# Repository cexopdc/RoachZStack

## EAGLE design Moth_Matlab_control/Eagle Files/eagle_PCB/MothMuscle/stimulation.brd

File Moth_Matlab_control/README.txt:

### Eagle ###
Inside the eagle folder are the board and schematic files for the device. The board is marked with what the components are.

### Control Software ###
streamer.m is the control software. Run the matlab file and it will open a gui that controls the tool set. 

LED arena is controlled via serial port. 
1. Connect the USB cable from the arduino to the computer
2. Use the matlab script transmitLED.m to send a command to the arena
3. Commands are formatted as "x#" where x is either "f" or "b" and # is a digit written as a string. 
	The "f" or "b" set the direction, and the time sets the speed

EMG recording
Connect the CC2531 dongle to the computer. Make sure you can see it in device manager. In the streamer GUI, the left side is to control the ADC. Enter a time in the box, select the COM port that corresponds to the USB dongle and hit open. Inside the gui this calls the transmitADC.m file which sends a control character and the time to the CC2530. This should start streaming back data for the desired amount of time. 

Stimulation
The transmitStimulate.m function is called from the gui. Enter the parameters in the text boxes and hit stimulate. This function reads the parameters, and sends them and a control character to the CC2530. The stimulation is controlled via GPIO pins set. 

Here is a list of characters from 'A' to 'P'. These 16 characters control which combination of electrodes are desired. 

    case 'A':
      POS_STIM1_SBIT = 0;
      POS_STIM2_SBIT = 0;
      POS_STIM3_SBIT = 0;
      POS_STIM4_SBIT = 0;
      break;
    case 'B':
      POS_STIM1_SBIT = 1;
      POS_STIM2_SBIT = 0;
      POS_STIM3_SBIT = 0;
      POS_STIM4_SBIT = 0;
      break;
    case 'C':
      POS_STIM1_SBIT = 0;
      POS_STIM2_SBIT = 1;
      POS_STIM3_SBIT = 0;
      POS_STIM4_SBIT = 0;
      break;
     case 'D':
      POS_STIM1_SBIT = 1;
      POS_STIM2_SBIT = 1;
      POS_STIM3_SBIT = 0;
      POS_STIM4_SBIT = 0;
      break;
     case 'E':
      POS_STIM1_SBIT = 0;
      POS_STIM2_SBIT = 0;
      POS_STIM3_SBIT = 1;
      POS_STIM4_SBIT = 0;
      break;
    case 'F':
      POS_STIM1_SBIT = 1;
      POS_STIM2_SBIT = 0;
      POS_STIM3_SBIT = 1;
      POS_STIM4_SBIT = 0;
      break;
    case 'G':
      POS_STIM1_SBIT = 0;
      POS_STIM2_SBIT = 1;
      POS_STIM3_SBIT = 1;
      POS_STIM4_SBIT = 0;
      break;
     case 'H':
      POS_STIM1_SBIT = 1;
      POS_STIM2_SBIT = 1;
      POS_STIM3_SBIT = 1;
      POS_STIM4_SBIT = 0;
      break;
    case 'I':
      POS_STIM1_SBIT = 0;
      POS_STIM2_SBIT = 0;
      POS_STIM3_SBIT = 0;
      POS_STIM4_SBIT = 1;
      break;
    case 'J':
      POS_STIM1_SBIT = 1;
      POS_STIM2_SBIT = 0;
      POS_STIM3_SBIT = 0;
      POS_STIM4_SBIT = 1;
      break;
    case 'K':
      POS_STIM1_SBIT = 0;
      POS_STIM2_SBIT = 1;
      POS_STIM3_SBIT = 0;
      POS_STIM4_SBIT = 1;
      break;
     case 'L':
      POS_STIM1_SBIT = 1;
      POS_STIM2_SBIT = 1;
      POS_STIM3_SBIT = 0;
      POS_STIM4_SBIT = 1;
      break;
    case 'M':
      POS_STIM1_SBIT = 0;
      POS_STIM2_SBIT = 0;
      POS_STIM3_SBIT = 1;
      POS_STIM4_SBIT = 1;
      break;
    case 'N':
      POS_STIM1_SBIT = 1;
      POS_STIM2_SBIT = 0;
      POS_STIM3_SBIT = 1;
      POS_STIM4_SBIT = 1;
      break;
    case 'O':
      POS_STIM1_SBIT = 0;
      POS_STIM2_SBIT = 1;
      POS_STIM3_SBIT = 1;
      POS_STIM4_SBIT = 1;
      break;
     case 'P':
      POS_STIM1_SBIT = 1;
      POS_STIM2_SBIT = 1;
      POS_STIM3_SBIT = 1;
      POS_STIM4_SBIT = 1;
      break;

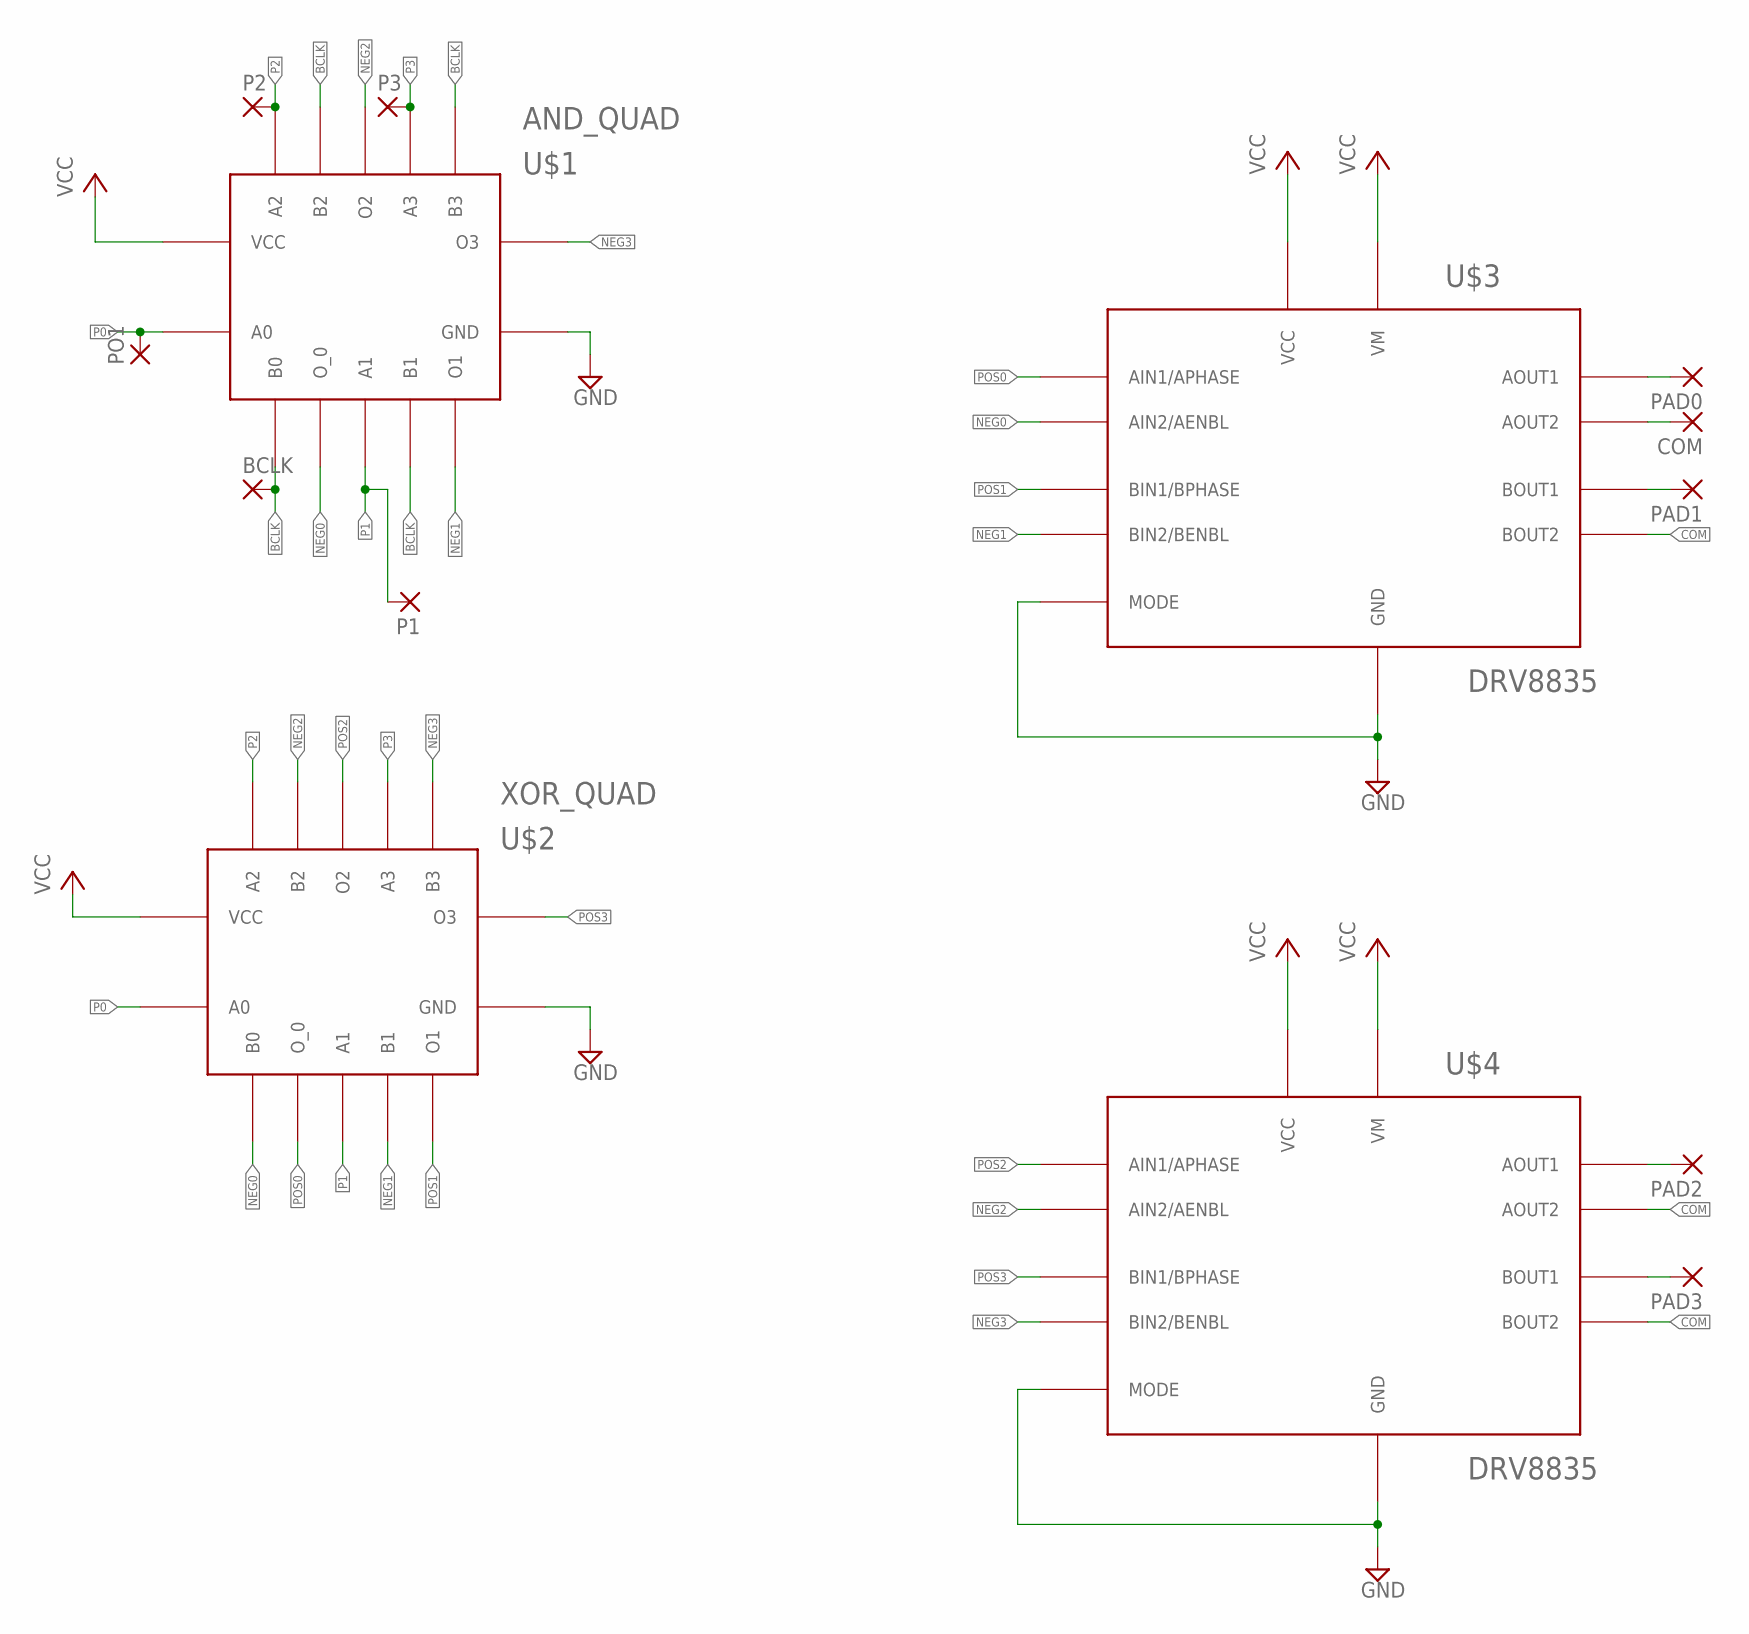
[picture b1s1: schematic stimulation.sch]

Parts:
BCLK: SMD2; SMD1,27-2,54
COM: SMD2; SMD1,27-2,54
P1, P2, P3: SMD2; SMD1,27-2,54
PAD0, PAD1, PAD2, PAD3: SMD2; SMD1,27-2,54
PO1: SMD2; SMD1,27-2,54
U$1: AND_QUAD; QFN-14
U$2: XOR_QUAD; QFN-14
U$3, U$4: DRV8835; QFN-12-HEATSINK

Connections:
BCLK: BCLK.1, U$1.B0, U$1.B1, U$1.B2, U$1.B3
COM: COM.1, U$3.AOUT2, U$3.BOUT2, U$4.AOUT2, U$4.BOUT2
GND: U$1.GND, U$2.GND, U$3.GND, U$3.MODE, U$4.GND, U$4.MODE
unnamed: P1.1, U$1.A1
unnamed: PAD0.1, U$3.AOUT1
unnamed: P2.1, U$1.A2
unnamed: PAD1.1, U$3.BOUT1
unnamed: P3.1, U$1.A3
unnamed: PO1.1, U$1.A0
unnamed: PAD2.1, U$4.AOUT1
unnamed: PAD3.1, U$4.BOUT1
NEG0: U$1.O_0, U$2.B0, U$3.AIN2.AENBL (AIN2/AENBL)
NEG1: U$1.O1, U$2.B1, U$3.BIN2/BENBL
NEG2: U$1.O2, U$2.B2, U$4.AIN2.AENBL (AIN2/AENBL)
NEG3: U$1.O3, U$2.B3, U$4.BIN2/BENBL
P0: U$2.A0
P1: U$2.A1
P2: U$2.A2
P3: U$2.A3
POS0: U$2.O_0, U$3.AIN1/APHASE
POS1: U$2.O1, U$3.BIN1/BPHASE
POS2: U$2.O2, U$4.AIN1/APHASE
POS3: U$2.O3, U$4.BIN1/BPHASE
VCC: U$1.VCC, U$2.VCC, U$3.VCC, U$3.VM, U$4.VCC, U$4.VM

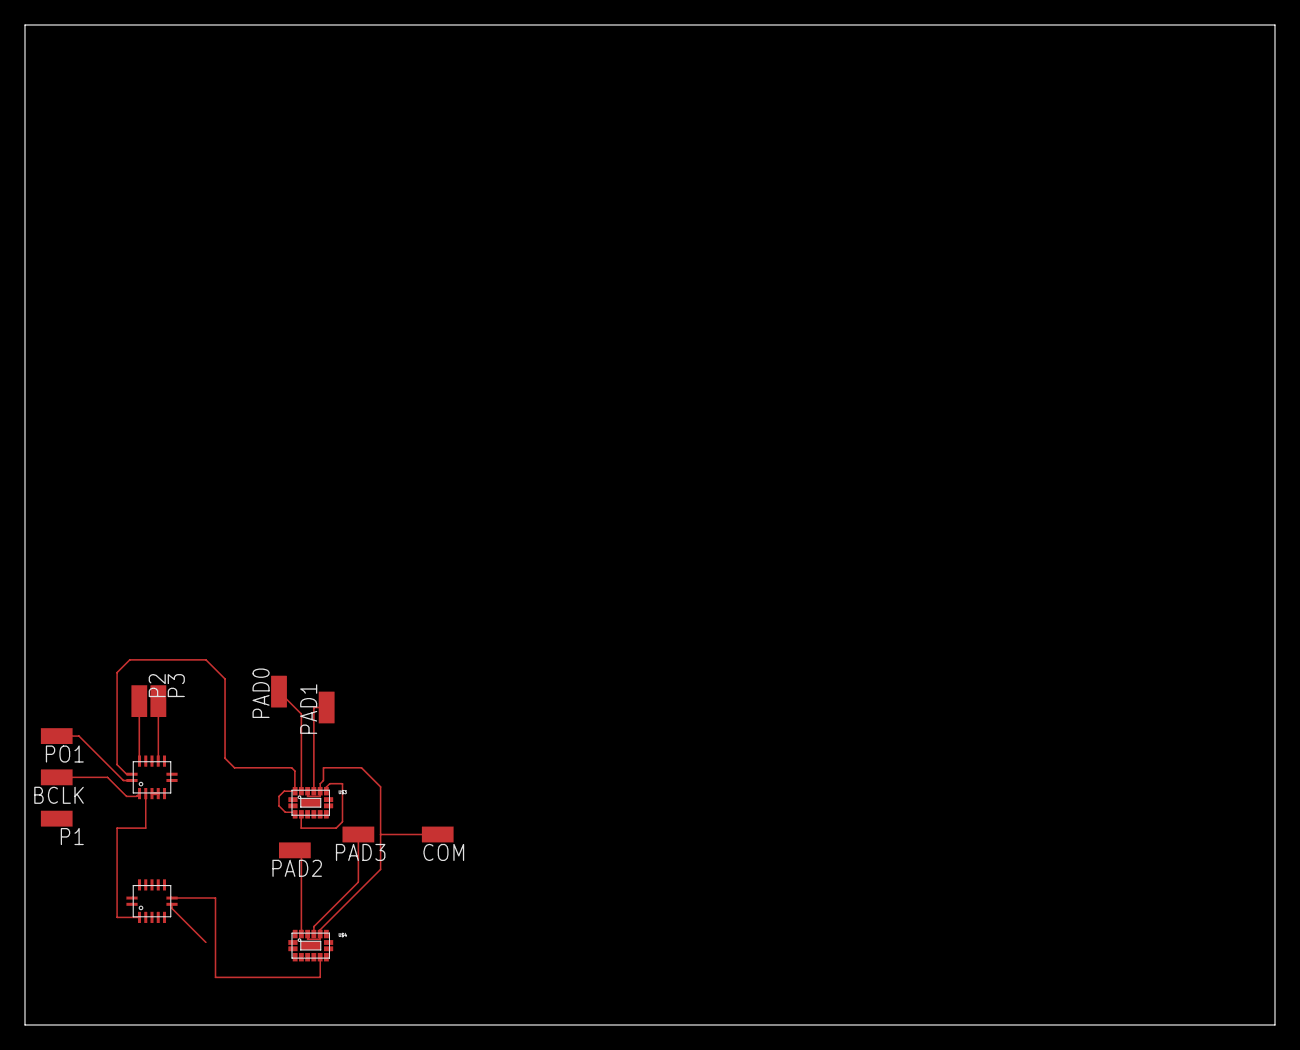
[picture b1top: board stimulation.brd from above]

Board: 2 copper layers, 100.0 x 80.0 mm, 14 parts (0 on the bottom side), 20 nets.

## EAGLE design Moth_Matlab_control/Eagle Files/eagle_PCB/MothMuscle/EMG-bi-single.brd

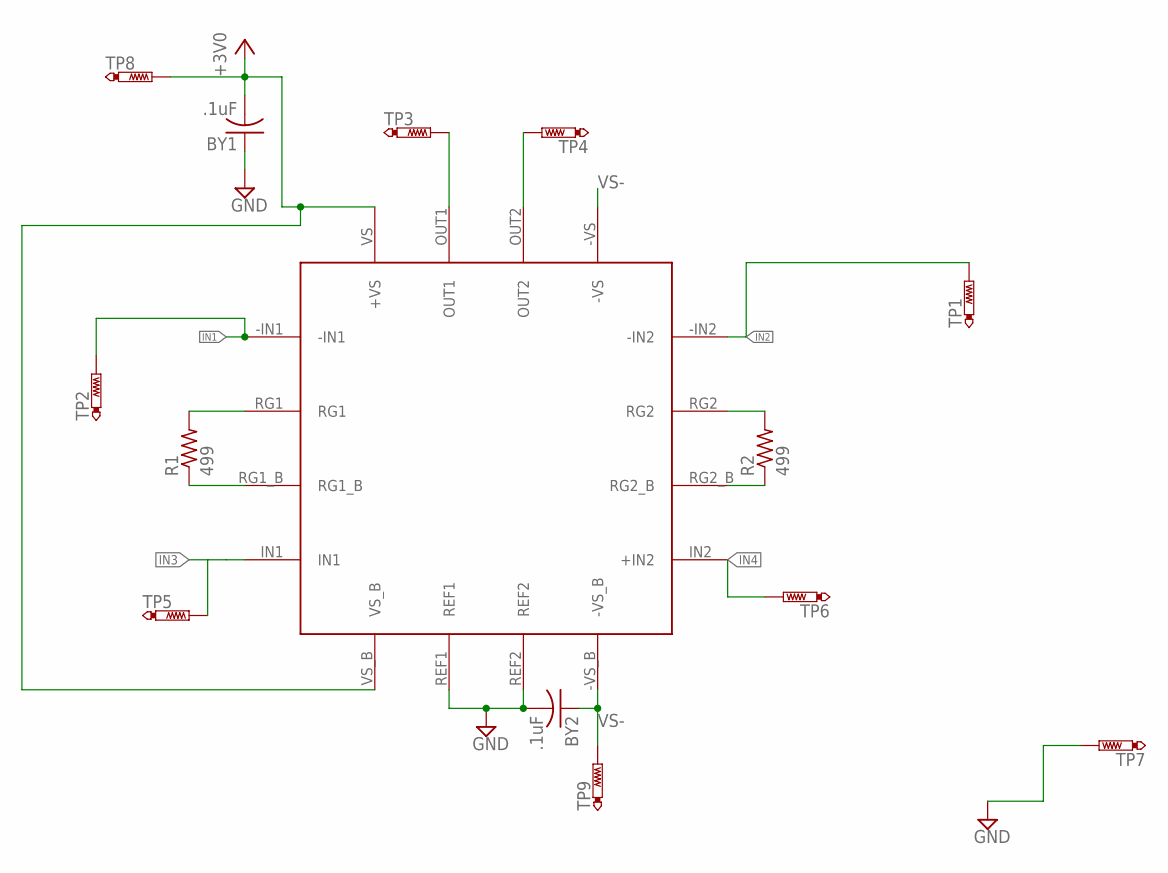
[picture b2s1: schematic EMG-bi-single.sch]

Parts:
BY1, BY2: .1uF; C0805
R1, R2: 499; R0805
TP1, TP2, TP3, TP4, TP5, TP6, TP7, TP8, TP9: PTR1TP20SQ; TP20SQ
U$9: AD8222; QFN-16

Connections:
+3V0: BY1.2, TP8.TP, U$9.VS (+VS), U$9.VS_B
GND: BY1.1, BY2.2, TP7.TP, U$9.REF1, U$9.REF2
IN1: TP2.TP, U$9.-IN1
IN2: TP1.TP, U$9.-IN2
IN3: TP5.TP, U$9.IN1
IN4: TP6.TP, U$9.IN2 (+IN2)
unnamed: R1.2, U$9.RG1
unnamed: R1.1, U$9.RG1_B
unnamed: R2.2, U$9.RG2
unnamed: TP3.TP, U$9.OUT1
unnamed: R2.1, U$9.RG2_B
unnamed: TP4.TP, U$9.OUT2
VS-: BY2.1, TP9.TP, U$9.-VS, U$9.-VS_B

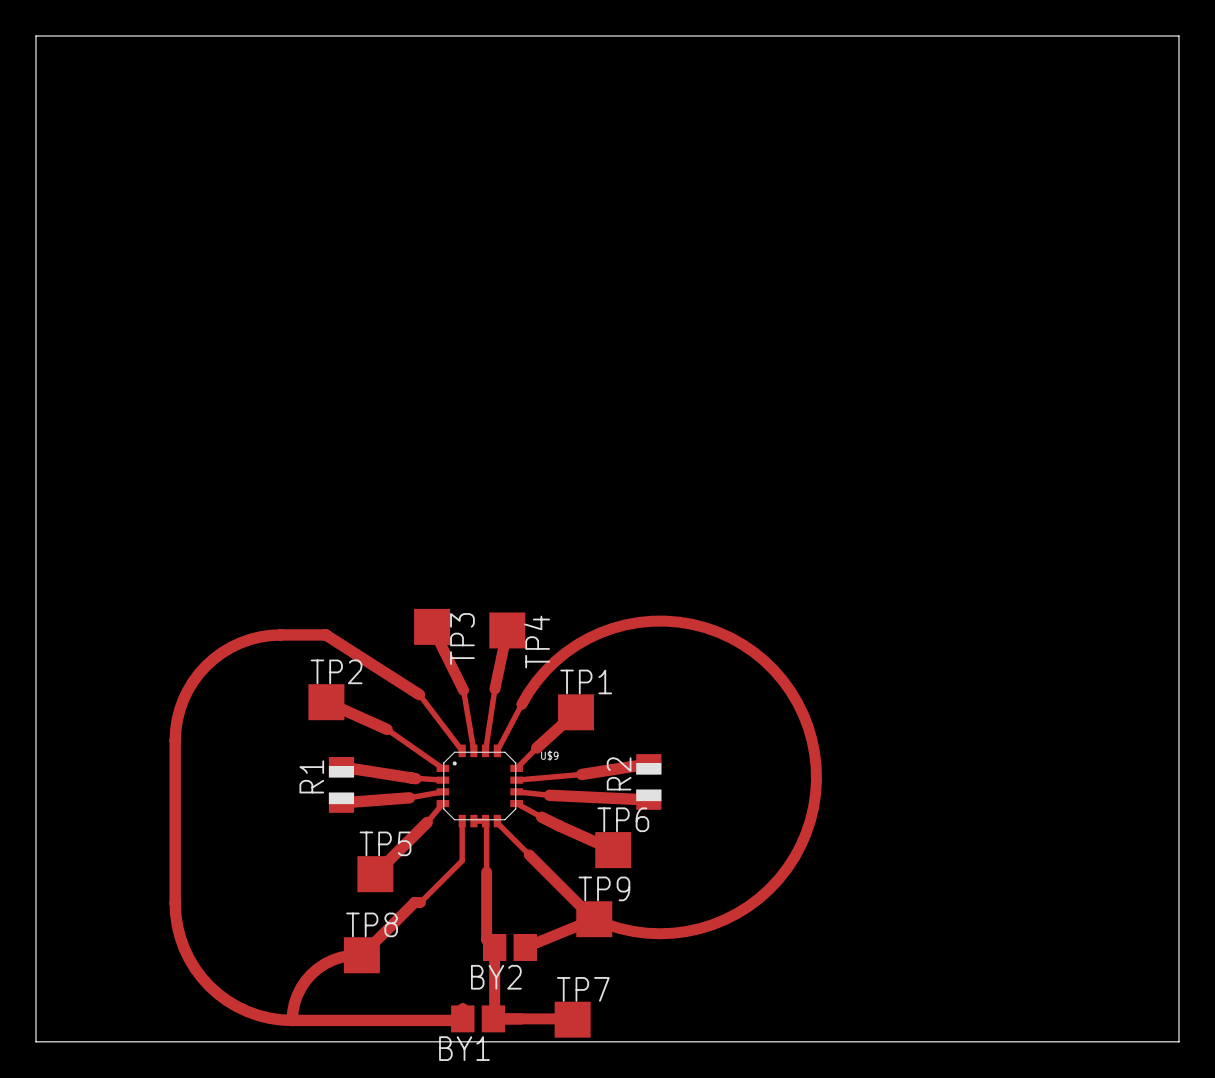
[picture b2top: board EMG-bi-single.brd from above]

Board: 2 copper layers, 63.5 x 55.9 mm, 14 parts (0 on the bottom side), 13 nets.

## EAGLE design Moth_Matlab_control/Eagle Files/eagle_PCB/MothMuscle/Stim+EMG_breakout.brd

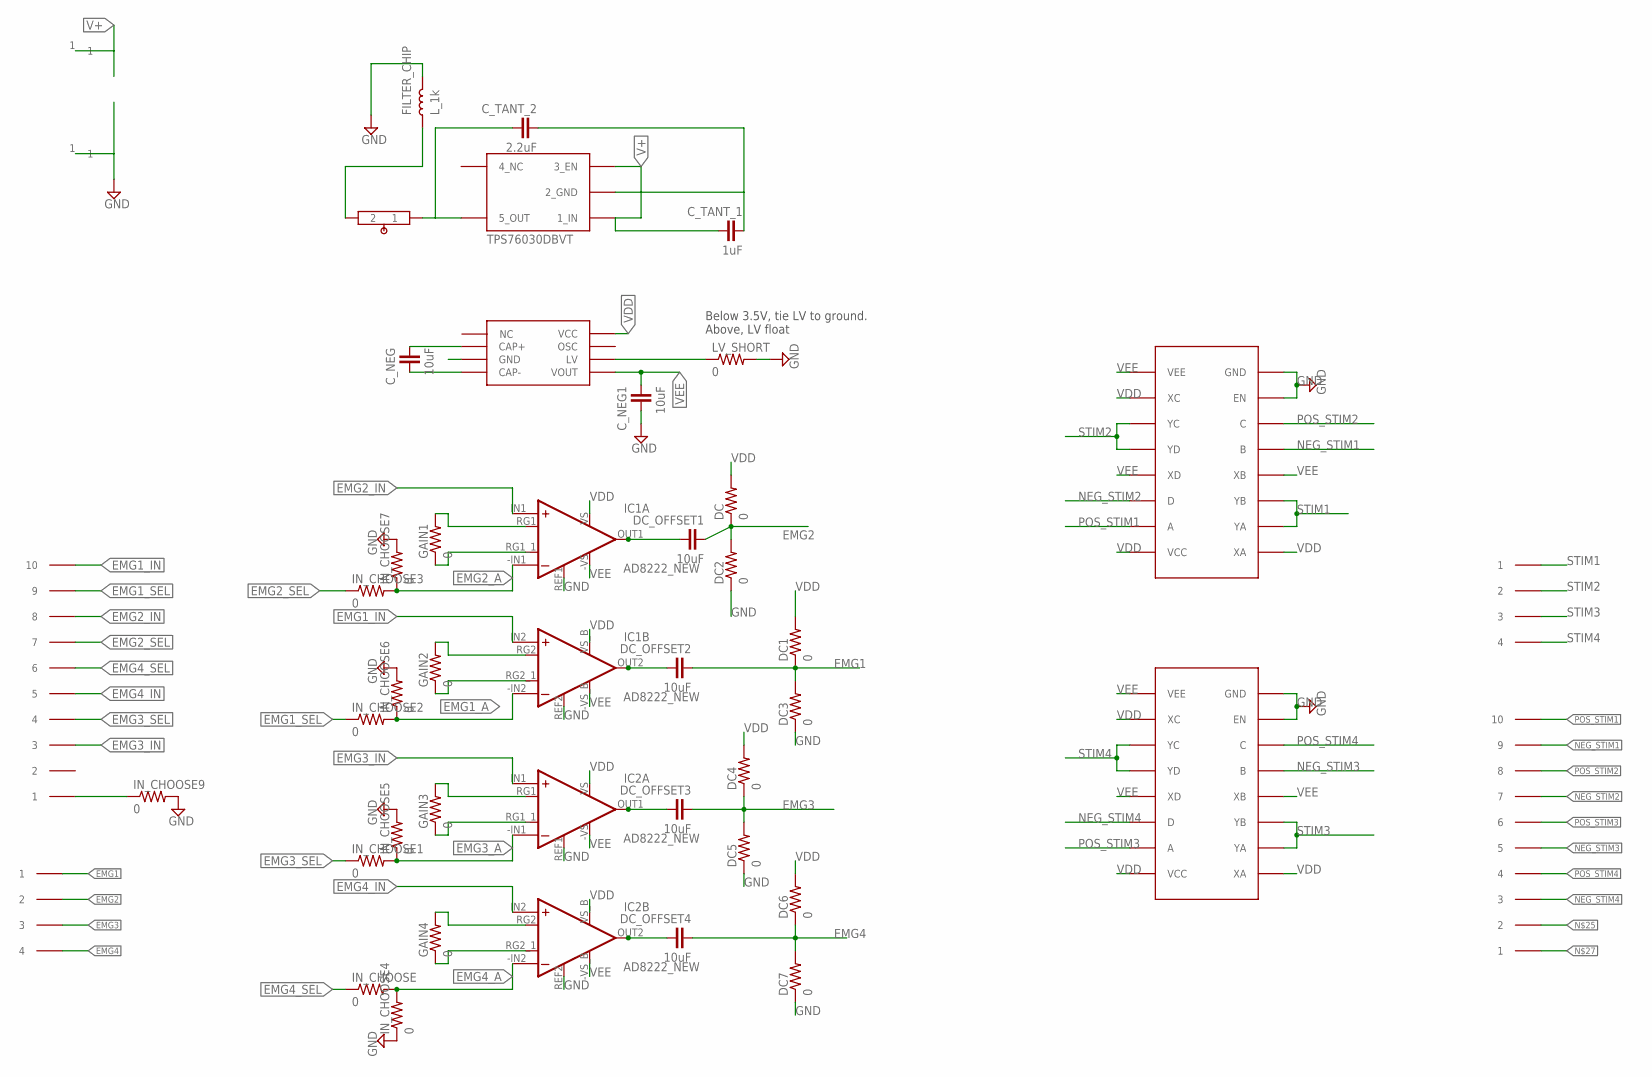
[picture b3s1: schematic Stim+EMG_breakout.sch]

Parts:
C_NEG, C_NEG1: 10uF; 0402_R/L/C
C_TANT_1: 1uF; 0603_R/L/C
C_TANT_2: 2.2uF; 0603_R/L/C
DC, DC1, DC2, DC3, DC4, DC5, DC6, DC7: 0; 0402_R/L/C
DC_OFFSET1, DC_OFFSET2, DC_OFFSET3, DC_OFFSET4: 10uF; 0402_R/L/C
FILTER_CHIP: L_1k; 0402_R/L/C
GAIN1, GAIN2, GAIN3, GAIN4: 0; 0402_R/L/C
IC1, IC2: AD8222_NEW; QFN-16
IN_CHOOSE, IN_CHOOSE1, IN_CHOOSE2, IN_CHOOSE3, IN_CHOOSE4, IN_CHOOSE5, IN_CHOOSE6, IN_CHOOSE7, IN_CHOOSE9: 0; 0201_R/L/C
LV_SHORT: 0; 0402_R/L/C
U$1, U$7: FFC10POS
U$2, U$28: FFC4POS
U$4: TL7660; S-PDSO-G8
U$5, U$6: MC74HC4316A; SOIC-16-ON-SEMI
U$10: REGULATOR
U$18: SWITCH_MANUAL
WIRE+: DRILL_CONNECT
WIRE-: DRILL_CONNECT

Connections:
EMG1: DC1.1, DC3.2, DC_OFFSET2.2, U$2.1
EMG1_A: IC1.-IN2 (-IN), IN_CHOOSE2.2, IN_CHOOSE6.1
EMG1_IN: IC1.IN2 (+IN), U$7.10
EMG1_SEL: IN_CHOOSE2.1, U$7.9
EMG2: DC.1, DC2.2, DC_OFFSET1.2, U$2.2
EMG2_A: IC1.-IN1 (-IN), IN_CHOOSE3.2, IN_CHOOSE7.1
EMG2_IN: IC1.IN1 (+IN), U$7.8
EMG2_SEL: IN_CHOOSE3.1, U$7.7
EMG3: DC4.1, DC5.2, DC_OFFSET3.2, U$2.3
EMG3_A: IC2.-IN1 (-IN), IN_CHOOSE1.2, IN_CHOOSE5.1
EMG3_IN: IC2.IN1 (+IN), U$7.3
EMG3_SEL: IN_CHOOSE1.1, U$7.4
EMG4: DC6.1, DC7.2, DC_OFFSET4.2, U$2.4
EMG4_A: IC2.-IN2 (-IN), IN_CHOOSE.2, IN_CHOOSE4.2
EMG4_IN: IC2.IN2 (+IN), U$7.5
EMG4_SEL: IN_CHOOSE.1, U$7.6
GND: C_NEG1.1, DC2.1, DC3.1, DC5.1, DC7.1, FILTER_CHIP.2, IC1.REF1 (REF), IC1.REF2 (REF), IC2.REF1 (REF), IC2.REF2 (REF), IN_CHOOSE4.1, IN_CHOOSE5.2, IN_CHOOSE6.2, IN_CHOOSE7.2, IN_CHOOSE9.2, LV_SHORT.2, U$4.3 (GND), U$5.7 (EN), U$5.8 (GND), U$6.7 (EN), U$6.8 (GND), WIRE-.1
unnamed: C_NEG.2, U$4.2 (CAP+)
unnamed: C_NEG.1, U$4.4 (CAP-)
unnamed: LV_SHORT.1, U$4.6 (LV)
unnamed: GAIN1.2, IC1.RG1
unnamed: GAIN1.1, IC1.RG1_1
unnamed: GAIN2.2, IC1.RG2 (RG1)
unnamed: GAIN2.1, IC1.RG2_1 (RG1_1)
unnamed: GAIN3.2, IC2.RG1
unnamed: GAIN3.1, IC2.RG1_1
unnamed: GAIN4.2, IC2.RG2 (RG1)
unnamed: GAIN4.1, IC2.RG2_1 (RG1_1)
unnamed: DC_OFFSET1.1, IC1.OUT1 (OUT)
unnamed: DC_OFFSET2.1, IC1.OUT2 (OUT)
unnamed: DC_OFFSET4.1, IC2.OUT2 (OUT)
unnamed: DC_OFFSET3.1, IC2.OUT1 (OUT)
unnamed: C_TANT_2.1, U$10.5 (5_OUT), U$18.1
unnamed: C_TANT_1.2, C_TANT_2.2, U$10.2 (2_GND)
unnamed: IN_CHOOSE9.1, U$7.1
NC: U$4.1 (NC)
NEG_STIM1: U$1.9, U$5.5 (B)
NEG_STIM2: U$1.7, U$5.14 (D)
NEG_STIM3: U$1.5, U$6.5 (B)
NEG_STIM4: U$1.3, U$6.14 (D)
OSC: U$4.7 (OSC)
POS_STIM1: U$1.10, U$5.15 (A)
POS_STIM2: U$1.8, U$5.6 (C)
POS_STIM3: U$1.6, U$6.15 (A)
POS_STIM4: U$1.4, U$6.6 (C)
STIM1: U$5.2 (YA), U$5.3 (YB), U$28.1
STIM2: U$5.11 (YC), U$5.12 (YD), U$28.2
STIM3: U$6.2 (YA), U$6.3 (YB), U$28.3
STIM4: U$6.11 (YC), U$6.12 (YD), U$28.4
V+: C_TANT_1.1, U$10.1 (1_IN), U$10.3 (3_EN), WIRE+.1
VDD: DC.2, DC1.2, DC4.2, DC6.2, FILTER_CHIP.1, IC1.VS (V+), IC1.VS_B (V+), IC2.VS (V+), IC2.VS_B (V+), U$4.8 (VCC), U$5.1 (XA), U$5.10 (XC), U$5.16 (VCC), U$6.1 (XA), U$6.10 (XC), U$6.16 (VCC), U$18.2
VEE: C_NEG1.2, IC1.-VS (V-), IC1.-VS_B (V-), IC2.-VS (V-), IC2.-VS_B (V-), U$4.5 (VOUT), U$5.4 (XB), U$5.9 (VEE), U$5.13 (XD), U$6.4 (XB), U$6.9 (VEE), U$6.13 (XD)

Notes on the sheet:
Below 3.5V, tie LV to ground. Above, LV float

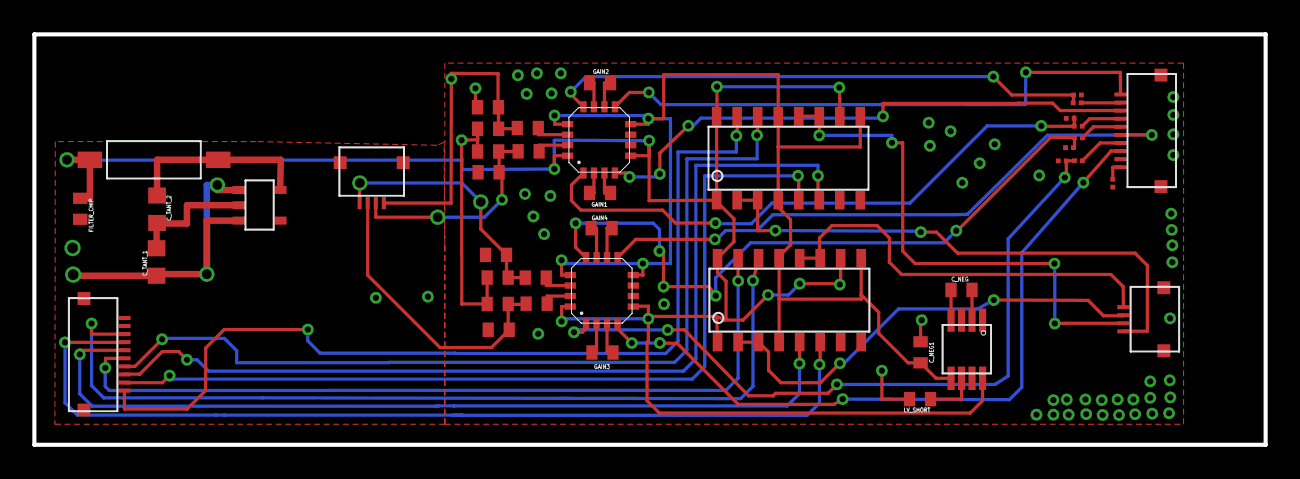
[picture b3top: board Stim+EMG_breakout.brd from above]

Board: 2 copper layers, 76.2 x 25.4 mm, 44 parts (0 on the bottom side), 50 nets.

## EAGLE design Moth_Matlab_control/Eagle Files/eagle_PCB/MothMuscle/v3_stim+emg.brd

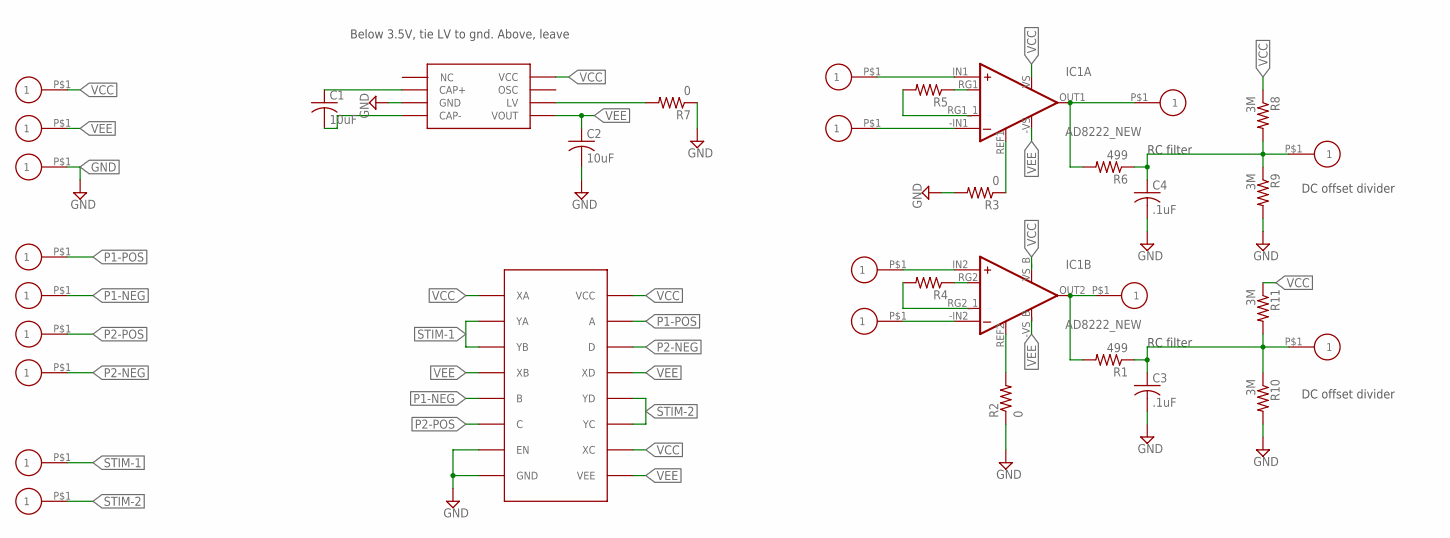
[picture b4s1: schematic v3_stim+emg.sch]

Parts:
A+: DBG_ELECTRODE
A-: DBG_ELECTRODE
A-OUT: DBG_ELECTRODE
B+: DBG_ELECTRODE
B-: DBG_ELECTRODE
B-OUT: DBG_ELECTRODE
C1, C2: 10uF; C0402
C3, C4: .1uF; C0402
EMG1, EMG2: DBG_ELECTRODE
GND: DBG_ELECTRODE
IC1: AD8222_NEW; QFN-16
P1-NEG, P1-POS, P2-NEG, P2-POS: DBG_ELECTRODE
R1, R6: 499; R0402
R2, R3, R7: 0; R0402
R4, R5: R-US_R0402; R0402
R8, R9, R10, R11: 3M; R0402
STIM-1, STIM-2: DBG_ELECTRODE
U$1: MC74HC4316A; SOIC-16-ON-SEMI
U$2: TL7660; S-PDSO-G8
VCC: DBG_ELECTRODE
VEE: DBG_ELECTRODE

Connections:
EMG1: C4.1, EMG1.P$1, R6.1, R8.2, R9.1
EMG2: C3.1, EMG2.P$1, R1.1, R10.1, R11.2
GND: C2.2, C3.2, C4.2, GND.P$1, R2.1, R3.2, R7.1, R9.2, R10.2, U$1.7 (EN), U$1.8 (GND), U$2.3 (GND)
unnamed: C1.1, U$2.2 (CAP+)
unnamed: C1.2, U$2.4 (CAP-)
unnamed: B+.P$1, IC1.IN2 (+IN)
unnamed: B-.P$1, IC1.-IN2 (-IN)
unnamed: R7.2, U$2.6 (LV)
unnamed: B-OUT.P$1, IC1.OUT2 (OUT), R1.2
unnamed: IC1.RG2 (RG1), R4.1
unnamed: IC1.RG2_1 (RG1_1), R4.2
unnamed: IC1.REF1 (REF), R3.1
unnamed: IC1.RG1, R5.1
unnamed: IC1.RG1_1, R5.2
unnamed: IC1.REF2 (REF), R2.2
unnamed: A-OUT.P$1, IC1.OUT1 (OUT), R6.2
unnamed: A+.P$1, IC1.IN1 (+IN)
unnamed: A-.P$1, IC1.-IN1 (-IN)
NC: U$2.1 (NC)
OSC: U$2.7 (OSC)
P1-NEG: P1-NEG.P$1, U$1.5 (B)
P1-POS: P1-POS.P$1, U$1.15 (A)
P2-NEG: P2-NEG.P$1, U$1.14 (D)
P2-POS: P2-POS.P$1, U$1.6 (C)
STIM-1: STIM-1.P$1, U$1.2 (YA), U$1.3 (YB)
STIM-2: STIM-2.P$1, U$1.11 (YC), U$1.12 (YD)
VCC: IC1.VS (V+), IC1.VS_B (V+), R8.1, R11.1, U$1.1 (XA), U$1.10 (XC), U$1.16 (VCC), U$2.8 (VCC), VCC.P$1
VEE: C2.1, IC1.-VS (V-), IC1.-VS_B (V-), U$1.4 (XB), U$1.9 (VEE), U$1.13 (XD), U$2.5 (VOUT), VEE.P$1

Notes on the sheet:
Below 3.5V, tie LV to gnd. Above, leave
DC offset divider
RC filter

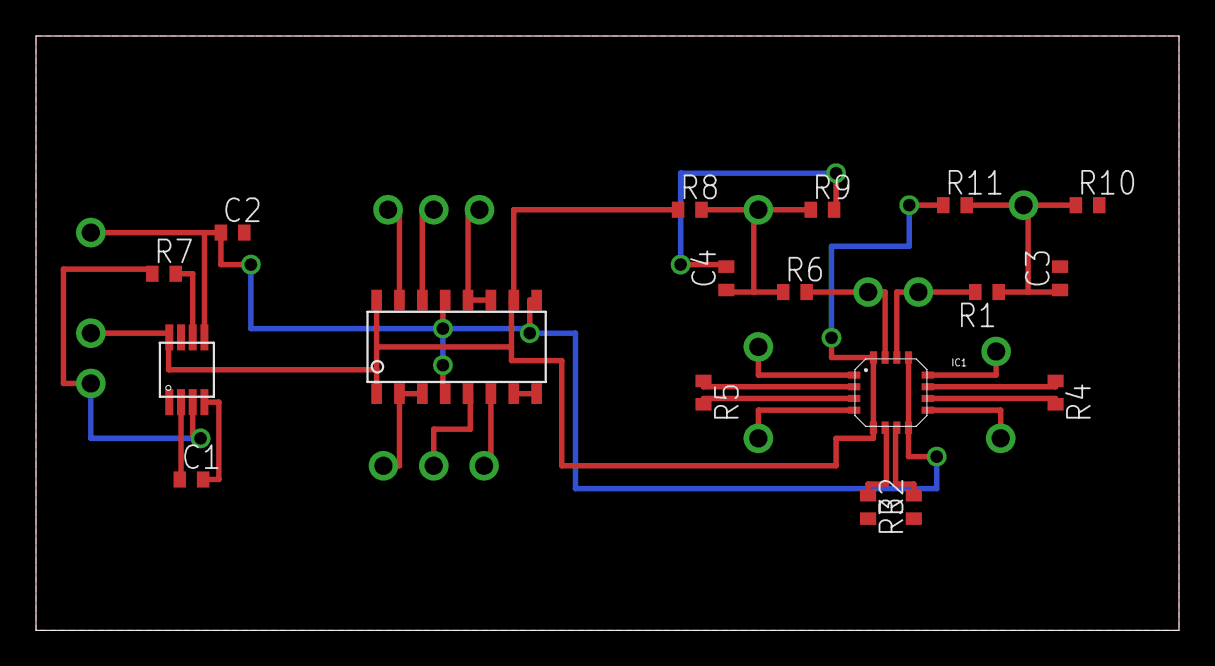
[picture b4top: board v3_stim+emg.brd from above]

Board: 2 copper layers, 63.5 x 33.0 mm, 35 parts (0 on the bottom side), 26 nets.

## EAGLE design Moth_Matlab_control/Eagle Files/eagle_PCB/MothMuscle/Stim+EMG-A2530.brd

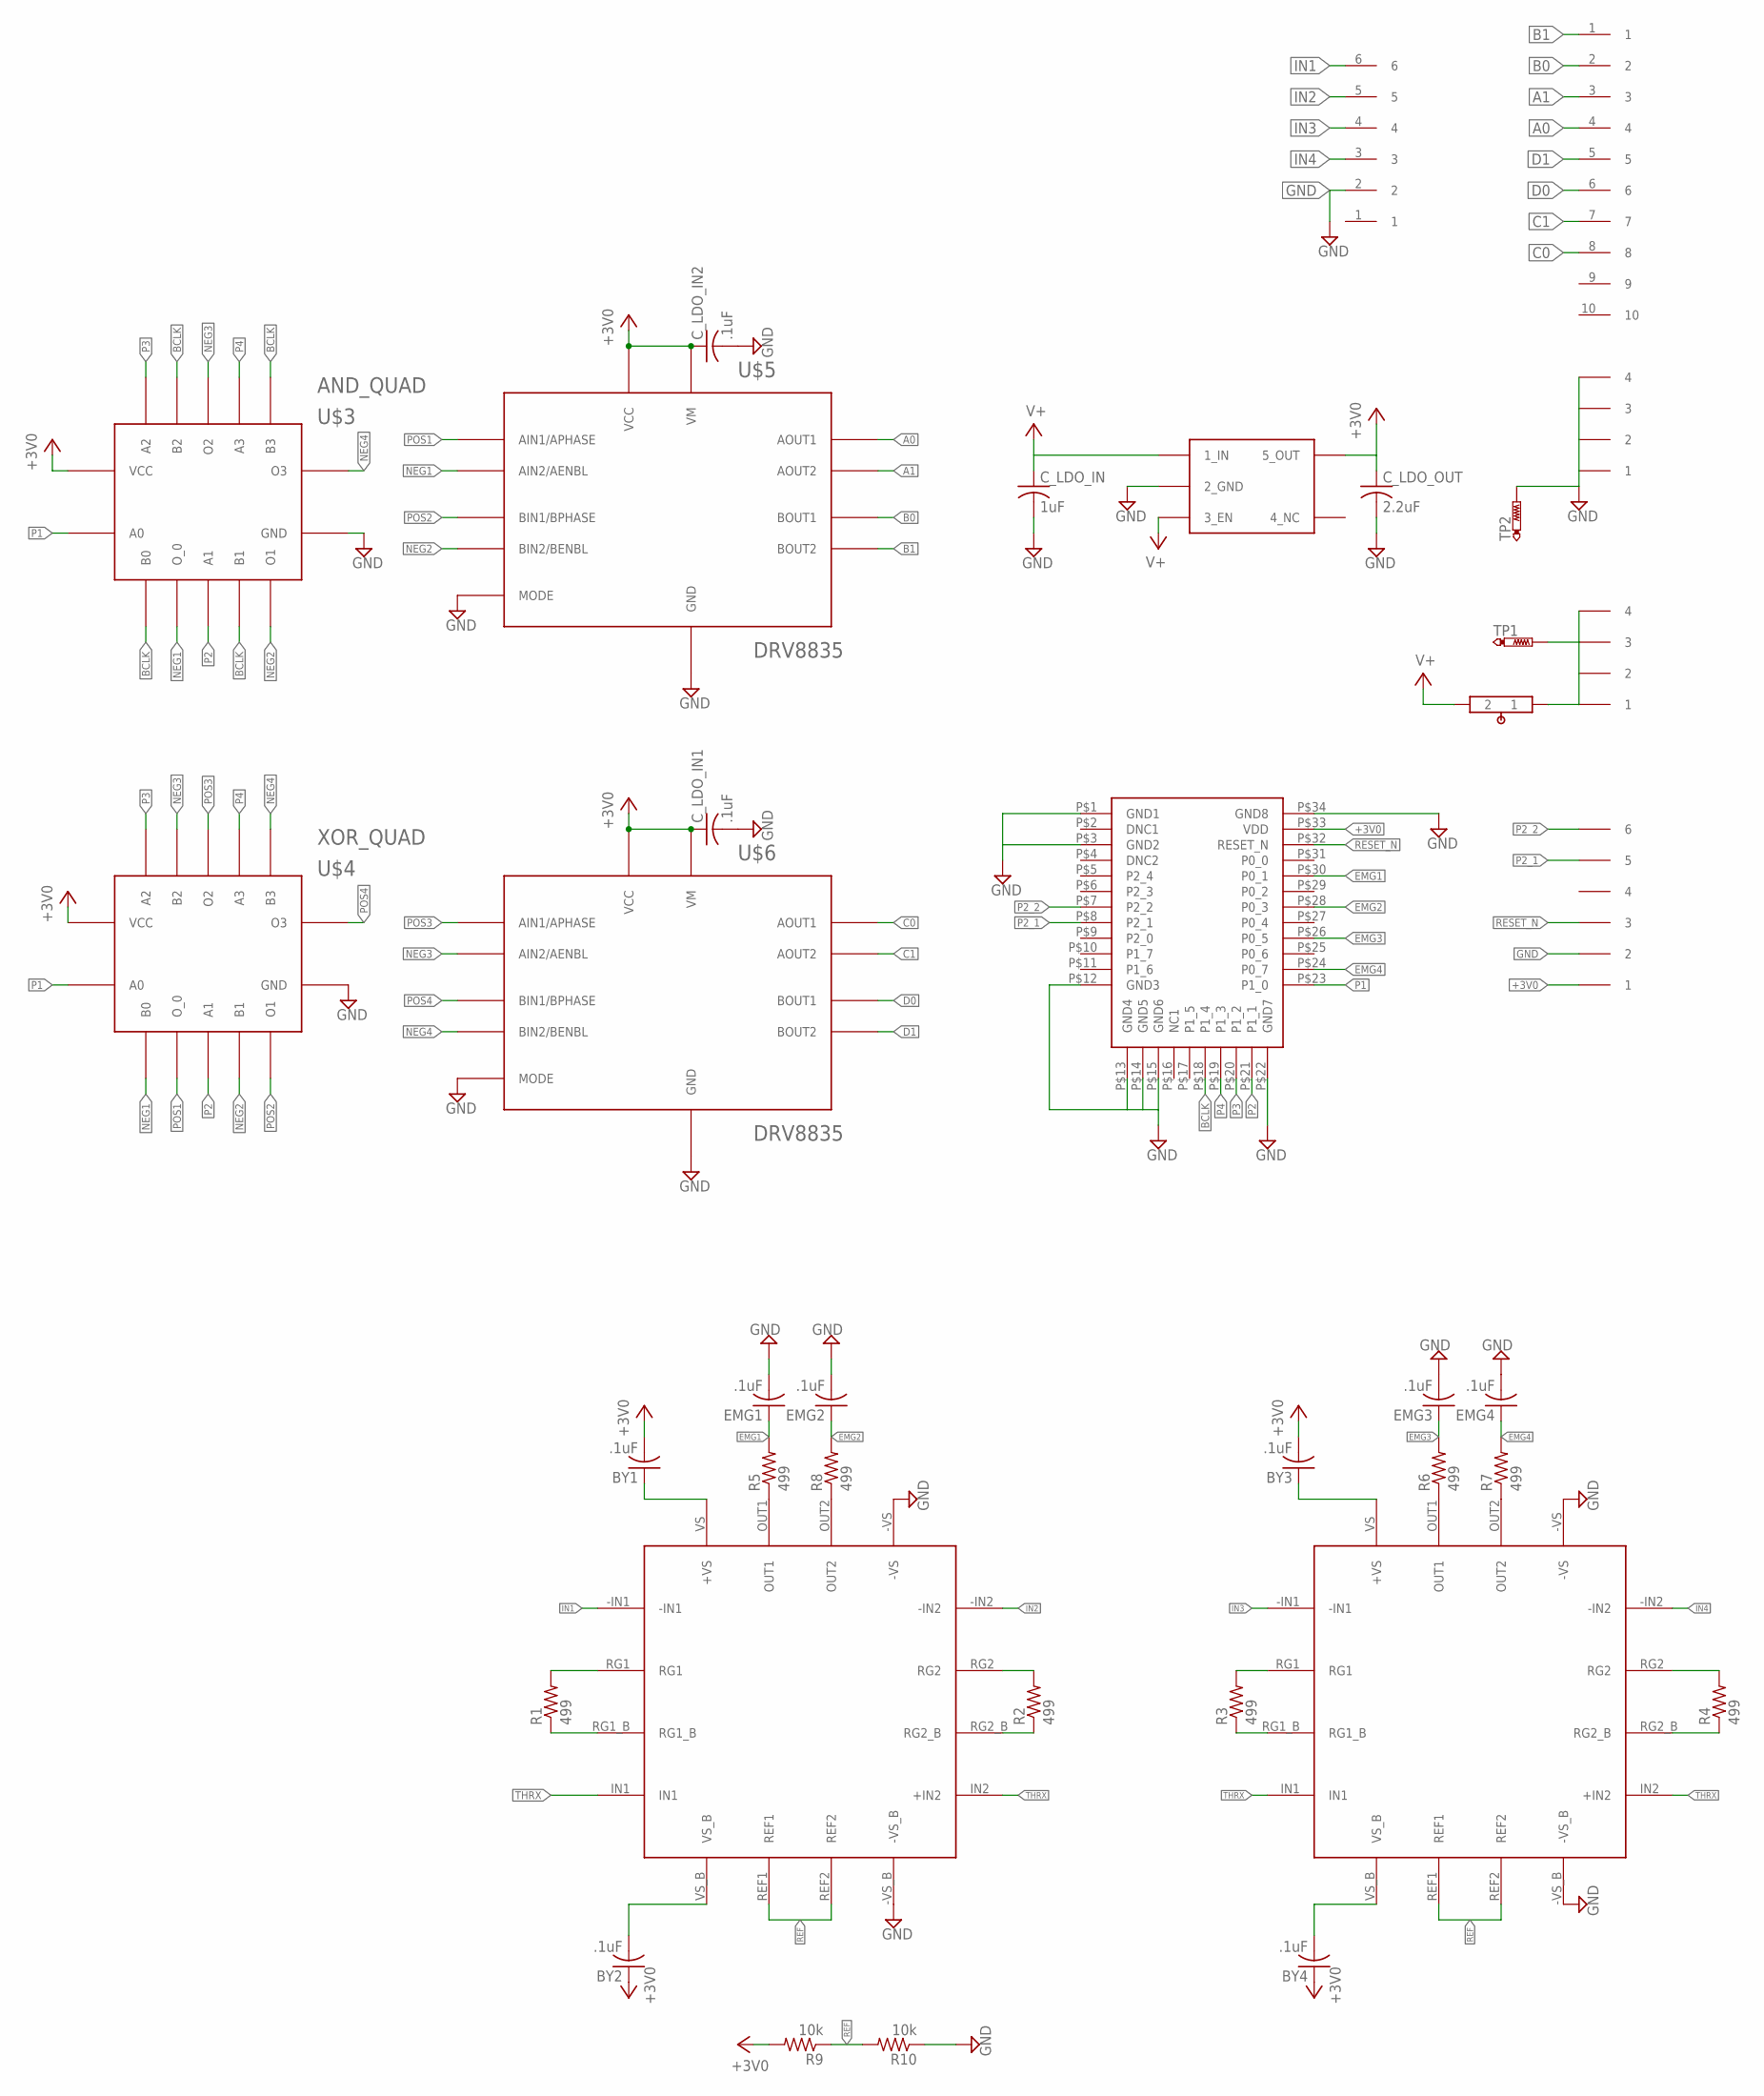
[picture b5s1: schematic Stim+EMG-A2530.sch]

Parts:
BY1, BY2, BY3, BY4: .1uF; C0603
C_LDO_IN: 1uF; C0603
C_LDO_IN1, C_LDO_IN2: .1uF; C0603
C_LDO_OUT: 2.2uF; C0603
EMG1, EMG2, EMG3, EMG4: .1uF; C0603
R1, R2, R3, R4, R5, R6, R7, R8: 499; R0402
R9, R10: 10k; R0402
TP1, TP2: PTR1B2,54; B2,54
U$1: A2530
U$2, U$12: FFC6POS
U$3: AND_QUAD; QFN-14
U$4: XOR_QUAD; QFN-14
U$5, U$6: DRV8835; QFN-12-HEATSINK
U$7, U$8: FFC4POS
U$9, U$10: AD8222; QFN-16
U$11: FFC10POS
U$18: SWITCH_MANUAL
VREG1: REGULATOR

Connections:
+3V0: C_LDO_OUT.1, U$1.P$33 (VDD), U$2.1, VREG1.5 (5_OUT)
+3V3: BY1.2, BY2.1, BY3.2, BY4.1, C_LDO_IN1.1, C_LDO_IN2.1, R9.2, U$3.VCC, U$4.VCC, U$5.VCC, U$5.VM, U$6.VCC, U$6.VM
A0: U$5.AOUT1, U$11.4
A1: U$5.AOUT2, U$11.3
B0: U$5.BOUT1, U$11.2
B1: U$5.BOUT2, U$11.1
BCLK: U$1.P$18 (P1_4), U$3.B0, U$3.B1, U$3.B2, U$3.B3
C0: U$6.AOUT1, U$11.8
C1: U$6.AOUT2, U$11.7
D0: U$6.BOUT1, U$11.6
D1: U$6.BOUT2, U$11.5
EMG1: EMG1.1, R5.2, U$1.P$30 (P0_1)
EMG2: EMG2.1, R8.2, U$1.P$28 (P0_3)
EMG3: EMG3.1, R6.2, U$1.P$26 (P0_5)
EMG4: EMG4.1, R7.2, U$1.P$24 (P0_7)
GND: C_LDO_IN.2, C_LDO_IN1.2, C_LDO_IN2.2, C_LDO_OUT.2, EMG1.2, EMG2.2, EMG3.2, EMG4.2, R10.1, TP2.TP, U$1.P$1 (GND1), U$1.P$3 (GND2), U$1.P$12 (GND3), U$1.P$13 (GND4), U$1.P$14 (GND5), U$1.P$15 (GND6), U$1.P$22 (GND7), U$1.P$34 (GND8), U$2.2, U$3.GND, U$4.GND, U$5.GND, U$5.MODE, U$6.GND, U$6.MODE, U$8.1, U$8.2, U$8.3, U$8.4, U$9.-VS, U$9.-VS_B, U$10.-VS, U$10.-VS_B, U$12.2, VREG1.2 (2_GND)
IN1: U$9.-IN1, U$12.6
IN2: U$9.-IN2, U$12.5
IN3: U$10.-IN1, U$12.4
IN4: U$10.-IN2, U$12.3
unnamed: R1.2, U$9.RG1
unnamed: R1.1, U$9.RG1_B
unnamed: R2.2, U$9.RG2
unnamed: TP1.TP, U$7.1, U$7.2, U$7.3, U$7.4, U$18.1
unnamed: R2.1, U$9.RG2_B
unnamed: R3.2, U$10.RG1
unnamed: R3.1, U$10.RG1_B
unnamed: R4.2, U$10.RG2
unnamed: R4.1, U$10.RG2_B
unnamed: R5.1, U$9.OUT1
unnamed: R8.1, U$9.OUT2
unnamed: R6.1, U$10.OUT1
unnamed: R7.1, U$10.OUT2
unnamed: BY1.1, U$9.VS (+VS)
unnamed: BY3.1, U$10.VS (+VS)
unnamed: BY4.2, U$10.VS_B
unnamed: BY2.2, U$9.VS_B
NEG1: U$3.O_0, U$4.B0, U$5.AIN2.AENBL (AIN2/AENBL)
NEG2: U$3.O1, U$4.B1, U$5.BIN2/BENBL
NEG3: U$3.O2, U$4.B2, U$6.AIN2.AENBL (AIN2/AENBL)
NEG4: U$3.O3, U$4.B3, U$6.BIN2/BENBL
P1: U$1.P$23 (P1_0), U$3.A0, U$4.A0
P2: U$1.P$21 (P1_1), U$3.A1, U$4.A1
P2_1: U$1.P$8 (P2_1), U$2.5
P2_2: U$1.P$7 (P2_2), U$2.6
P3: U$1.P$20 (P1_2), U$3.A2, U$4.A2
P4: U$1.P$19 (P1_3), U$3.A3, U$4.A3
POS1: U$4.O_0, U$5.AIN1/APHASE
POS2: U$4.O1, U$5.BIN1/BPHASE
POS3: U$4.O2, U$6.AIN1/APHASE
POS4: U$4.O3, U$6.BIN1/BPHASE
REF: R9.1, R10.2, U$9.REF1, U$9.REF2, U$10.REF1, U$10.REF2
RESET_N: U$1.P$32 (RESET_N), U$2.3
THRX: U$9.IN1, U$9.IN2 (+IN2), U$10.IN1, U$10.IN2 (+IN2)
V+: C_LDO_IN.1, U$18.2, VREG1.1 (1_IN), VREG1.3 (3_EN)
